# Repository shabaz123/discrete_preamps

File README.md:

# Discrete Amps

This repository contains  discrete audio amplifier designs intended primarily for HF receiver applications (speech bandwidth, not music).  

Each design includes:
- KiCad 10 Schematic and PCB files
- KiCad 10 SPICE Simulation Workbook
- Gerber files for fabrication  
- PDF schematic export and PCB screenshots for easy viewing without KiCad  

---

## Preamp K1

Designed by M. Kellett, this preamplifier is optimised for speech signals in HF receivers.

- **Gain:** ~28 dB  
- **Bandwidth (-3 dB):** ~150 Hz to 10 kHz (approximate)  
- **Use case:** Moderate gain front-end with relatively wide speech bandwidth  

### Schematic

### PCB Top

### PCB Underside

### PCB Render

---

## Preamp K2

Also designed by M. Kellett, this version provides higher gain and a slightly narrower bandwidth, making it suitable where additional amplification is required.

- **Gain:** ~45 dB  
- **Bandwidth (-3 dB):** ~100 Hz to 7 kHz (approximate)  
- **Use case:** Higher gain stage for weak signal amplification  

### Schematic

### PCB Top

### PCB Underside

### PCB Render

---

## Poweramp K1

Also designed by M. Kellett, this amplifier is a power stage, and it directly drives 8 ohm speakers, with low distortion (less than 0.5%) at 280 mW.

- **Gain:** ~27 dB  
- **Bandwidth (-3 dB):** ~50 Hz to 30 kHz (approximate)  
- **Use case:** Driving an 8-ohm speaker in a radio receiver  

### Schematic

### PCB Top

### PCB Underside

### PCB Render

---

## Notes

These designs are intended for experimentation and adaptation.

All components are easy to source. 

For the 9V power connection, the PCB will accomodate any 2-pin screw terminal block with 3.5 to 5.08 mm pin pitch. 

For the audio input and output, an AliExpress stereo audio jack socket can be used (only the tip and the screen is used, the ring is not connected). Alternatively, the audio connections can be made with 0.1" pin headers (they will fit in the same footprint, as there are extra holes for that). 

The potentiometer can be ALPS RK097 series (available from AliExpress), it has pins at 2.5 mm pitch, and a body width of 10 mm.

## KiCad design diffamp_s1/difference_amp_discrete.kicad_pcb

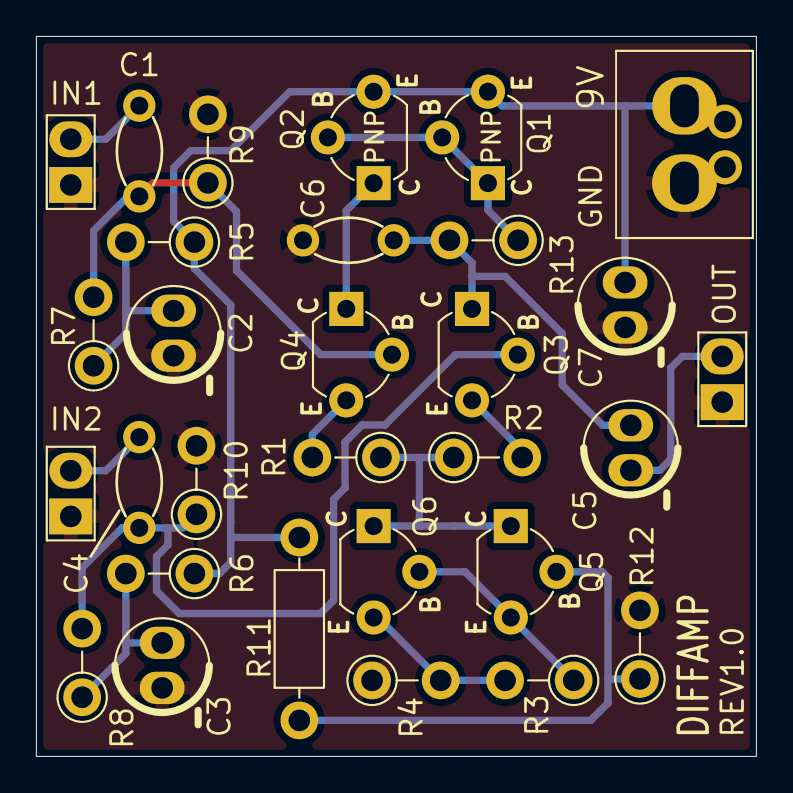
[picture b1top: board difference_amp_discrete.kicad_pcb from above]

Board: 2 copper layers, 40.0 x 40.0 mm, 30 parts (0 on the bottom side), 18 nets.

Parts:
C1, C4: 1u; C_Disc_T3.0mm_P5.0
C2, C3, C5, C7: 10u; CP_Radial_D5.0mm_P2.50mm
C6: 470p; C_Disc_T3.0mm_P5.0
J1: IN1; PinHeader_1x02_P2.54mm_Vertical
J2, J3: IN2; PinHeader_1x02_P2.54mm_Vertical
J4: 9VDC; TerminalBlock_2way-3.5-5.0mm
Q1, Q2: BC557; BJT_PNP_BC557
Q3, Q4, Q5, Q6: BC547; BJT_NPN_BC547
R1, R2, R3, R4: 470; R_Axial_L6.3mm_D2.5mm_P3.81mm_Vertical
R5, R6: 10k; R_Axial_L6.3mm_D2.5mm_P3.81mm_Vertical
R7, R8, R9, R10: 22k; R_Axial_L6.3mm_D2.5mm_P3.81mm_Vertical
R11: 2.7k; R_Axial_L6.3mm_D2.5mm_P10.16mm_Horiz
R12: 1k; R_Axial_L6.3mm_D2.5mm_P3.81mm_Vertical
R13: 3.3k; R_Axial_L6.3mm_D2.5mm_P3.81mm_Vertical

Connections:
0V: C2.2, C3.2, C6.1, C7.2, J1.1, J2.1, J3.1, J4.1, R4.1, R9.2, R10.2, R12.2
/IN1: C1.1, J1.2
/IN2: C4.2, J2.2
/OUT: C5.2, J3.2
unnamed: C2.1, R5.2, R7.1
unnamed: C3.1, R6.2, R8.1
unnamed: Q1.1 (C), Q1.2 (B), Q2.2 (B), R13.1
unnamed: Q2.1 (C), Q4.1 (C)
unnamed: C4.1, Q3.2 (B), R8.2, R10.1
unnamed: C5.1, C6.2, Q3.1 (C), R13.2
unnamed: Q3.3 (E), R2.2
unnamed: C1.2, Q4.2 (B), R7.2, R9.1
unnamed: Q4.3 (E), R1.2
unnamed: Q5.2 (B), R11.1, R12.1
unnamed: Q5.1 (C), Q6.1 (C), R1.1, R2.1
unnamed: Q5.3 (E), Q6.2 (B), R3.1
unnamed: Q6.3 (E), R3.2, R4.2
V+: C7.1, J4.2, Q1.3 (E), Q2.3 (E), R5.1, R6.1, R11.2

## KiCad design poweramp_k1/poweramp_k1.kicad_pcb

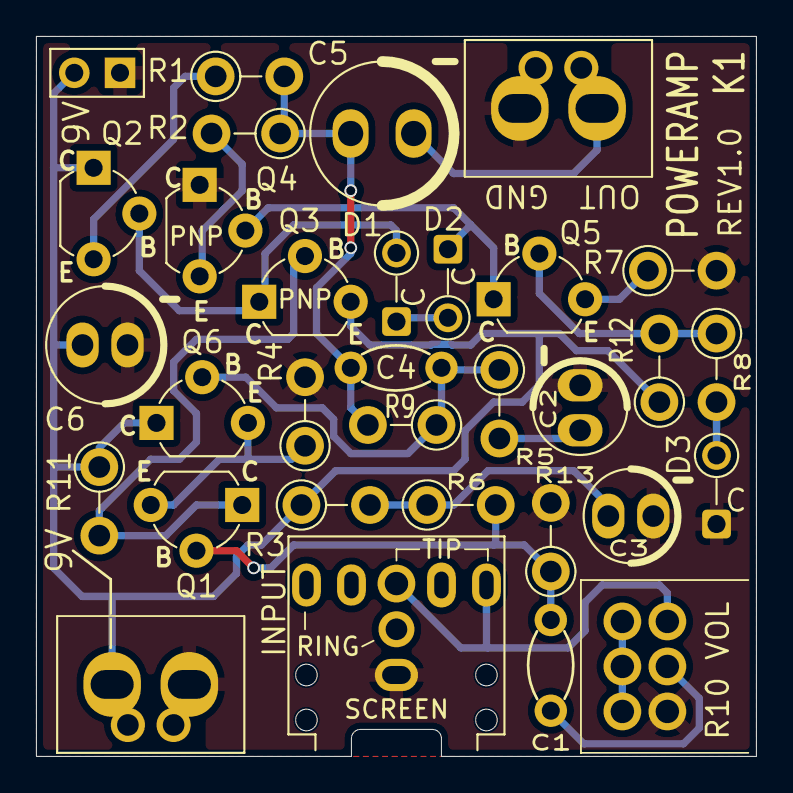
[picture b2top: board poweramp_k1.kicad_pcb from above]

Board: 2 copper layers, 40.0 x 40.0 mm, 32 parts (0 on the bottom side), 20 nets.

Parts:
C1: 220n; C_Disc_T3.0mm_P5.0
C2: 10u; CP_Radial_D5.0mm_P2.50mm
C3: 47u; CP_Radial_D5.0mm_P2.50mm
C4: 270p; C_Disc_T3.0mm_P5.0
C5: 470u; CP_Radial_D8mm_P3.5mm
C6: 100u; CP_Radial_D6.3mm_P2.50mm
D1, D2, D3: 1N4148; Diode-DO-35_1.75mmDia_P3.81mm_Vert_CathodeUp
J1: AudioJack_Stereo; Jack_3.5mm_CUI_SJ1-3525N_Horizontal
J3: 9VDC; TerminalBlock_2way-3.5-5.0mm
J4: PinHeader_1x02_P2.54mm_Vertical
J5: SPEAKER; TerminalBlock_2way-3.5-5.0mm
Q1, Q5, Q6: BC547; BJT_NPN_BC547
Q2: BC337-25; BJT_NPN_BC547
Q3: BC557; BJT_PNP_BC557
Q4: BC327-25; BJT_PNP_BC557
R1, R2: 2.2R; R_Axial_L6.3mm_D2.5mm_P3.81mm_Vertical
R3: 10k; R_Axial_L6.3mm_D2.5mm_P3.81mm_Vertical
R4: 1.5k; R_Axial_L6.3mm_D2.5mm_P3.81mm_Vertical
R5: 1k; R_Axial_L6.3mm_D2.5mm_P3.81mm_Vertical
R6: 33k; R_Axial_L6.3mm_D2.5mm_P3.81mm_Vertical
R7: 150R; R_Axial_L6.3mm_D2.5mm_P3.81mm_Vertical
R8: 2k; R_Axial_L6.3mm_D2.5mm_P3.81mm_Vertical
R9: 22k; R_Axial_L6.3mm_D2.5mm_P3.81mm_Vertical
R10: 22k; Potentiometer_RD701F
R11: 630R; R_Axial_L6.3mm_D2.5mm_P3.81mm_Vertical
R12: 27k; R_Axial_L6.3mm_D2.5mm_P3.81mm_Vertical
R13: 43k; R_Axial_L6.3mm_D2.5mm_P3.81mm_Vertical

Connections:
0V: C2.2, C3.2, C6.2, D3.1 (K), J1.S, J3.2, J4.1, J5.2, Q4.1 (C), R4.2, R7.2, R10.1, R13.2
/IN: J1.T, R10.3
/OUT: C5.2, J5.1
unnamed: C1.1, R10.2
unnamed: C2.1, R5.2
unnamed: C3.1, R3.2, R6.1
unnamed: C4.2, C5.1, R1.2, R2.1, R9.2
unnamed: D1.2 (A), Q2.2 (B), Q3.1 (C)
unnamed: D1.1 (K), D2.2 (A)
unnamed: D2.1 (K), Q4.2 (B), Q5.1 (C)
unnamed: D3.2 (A), R8.2
unnamed: C1.2, Q1.2 (B), R6.2, R13.1
unnamed: Q1.1 (C), Q3.2 (B), R11.2
unnamed: Q1.3 (E), Q6.3 (E), R4.1
unnamed: Q2.3 (E), R1.1
unnamed: Q4.3 (E), R2.2
unnamed: Q5.2 (B), R8.1, R12.2
unnamed: Q5.3 (E), R7.1
unnamed: C4.1, Q6.2 (B), R5.1, R9.1
V+: C6.1, J3.1, J4.2, Q2.1 (C), Q3.3 (E), Q6.1 (C), R3.1, R11.1, R12.1

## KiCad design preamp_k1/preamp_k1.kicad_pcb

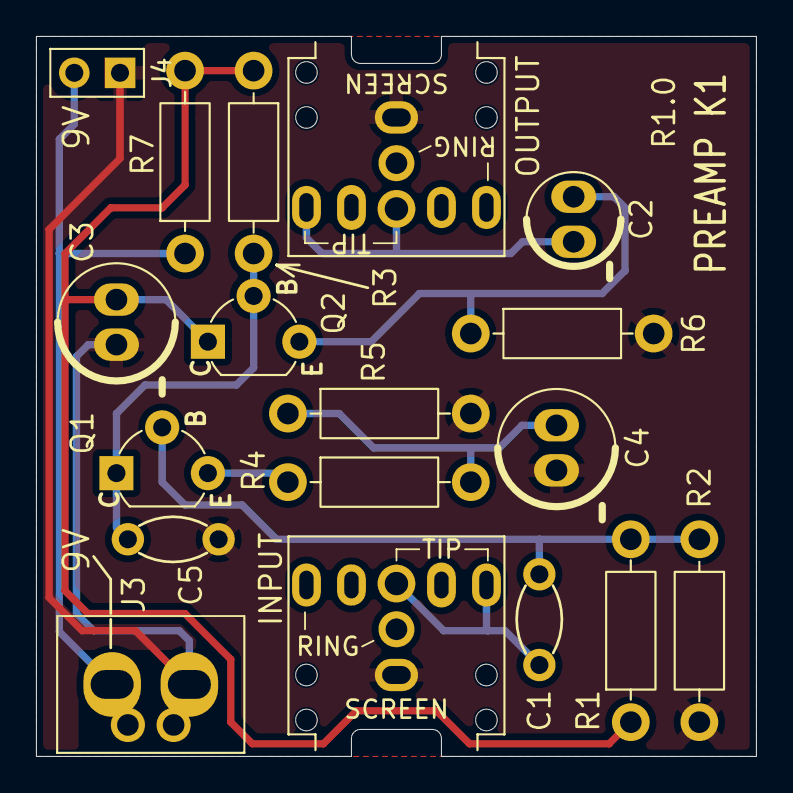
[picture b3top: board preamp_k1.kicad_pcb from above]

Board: 2 copper layers, 40.0 x 40.0 mm, 18 parts (0 on the bottom side), 10 nets.

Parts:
C1: 100n; C_Disc_T3.0mm_P5.0
C2: 4.7u; CP_Radial_D5.0mm_P2.50mm
C3: 47u; CP_Radial_D6.3mm_P2.50mm
C4: 4.7u; CP_Radial_D6.3mm_P2.50mm
C5: 10n; C_Disc_T3.0mm_P5.0
J1, J2: AudioJack_Stereo; Jack_3.5mm_CUI_SJ1-3525N_Horizontal
J3: 9VDC; TerminalBlock_2way-3.5-5.0mm
J4: PinHeader_1x02_P2.54mm_Vertical
Q1, Q2: BC549; BJT_NPN_BC547
R1: 100k; R_Axial_L6.3mm_D2.5mm_P10.16mm_Horiz
R2: 33k; R_Axial_L6.3mm_D2.5mm_P10.16mm_Horiz
R3: 2.2k; R_Axial_L6.3mm_D2.5mm_P10.16mm_Horiz
R4: 47R; R_Axial_L6.3mm_D2.5mm_P10.16mm_Horiz
R5: 910R; R_Axial_L6.3mm_D2.5mm_P10.16mm_Horiz
R6: 4.7k; R_Axial_L6.3mm_D2.5mm_P10.16mm_Horiz
R7: 1.2k; R_Axial_L6.3mm_D2.5mm_P10.16mm_Horiz

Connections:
0V: C3.2, C4.2, C5.1, J1.S, J2.S, J3.2, J4.1, R2.2, R5.2, R6.2
/IN: C1.1, J1.T
/OUT: C2.2, J2.T
unnamed: C4.1, R4.2, R5.1
unnamed: C1.2, Q1.2 (B), R1.2, R2.1
unnamed: C5.2, Q1.1 (C), Q2.2 (B), R3.2
unnamed: Q1.3 (E), R4.1
unnamed: C3.1, Q2.1 (C), R1.1, R3.1, R7.2
unnamed: C2.1, Q2.3 (E), R6.1
V+: J3.1, J4.2, R7.1

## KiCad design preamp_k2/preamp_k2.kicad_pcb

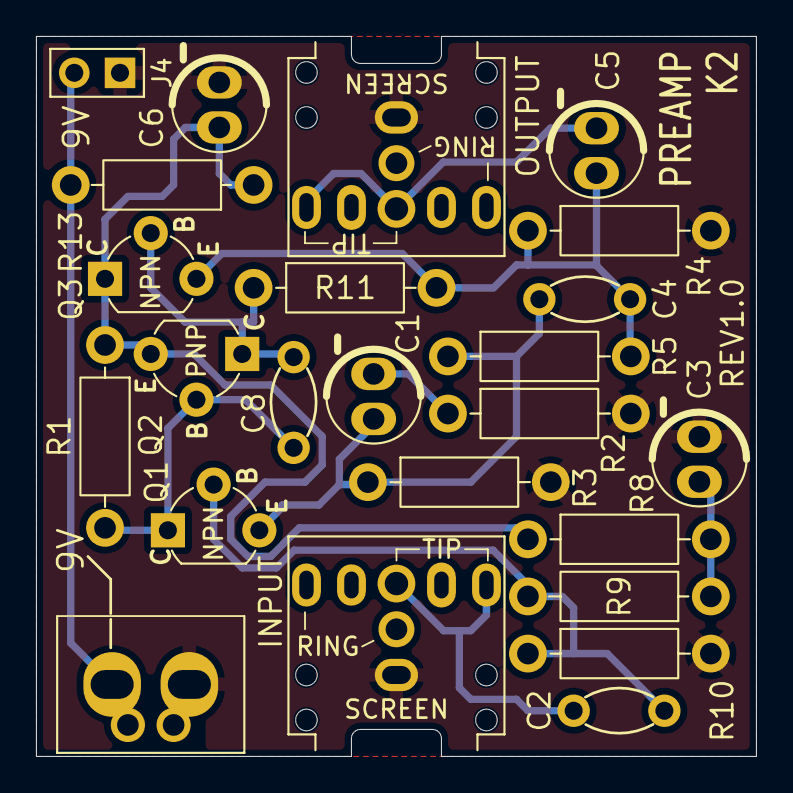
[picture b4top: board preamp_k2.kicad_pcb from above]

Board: 2 copper layers, 40.0 x 40.0 mm, 24 parts (0 on the bottom side), 12 nets.

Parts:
C1, C3, C6: 22u; CP_Radial_D5.0mm_P2.50mm
C2: 100n; C_Disc_T3.0mm_P5.0
C4: 2.2n; C_Disc_T3.0mm_P5.0
C5: 4.7u; CP_Radial_D5.0mm_P2.50mm
C8: 220p; C_Disc_T3.0mm_P5.0
J1, J2: AudioJack_Stereo; Jack_3.5mm_CUI_SJ1-3525N_Horizontal
J3: 9VDC; TerminalBlock_2way-3.5-5.0mm
J4: PinHeader_1x02_P2.54mm_Vertical
Q1, Q3: BC549; BJT_NPN_BC547
Q2: BC559; BJT_PNP_BC557
R1: 5.6k; R_Axial_L6.3mm_D2.5mm_P10.16mm_Horiz
R2: 82R; R_Axial_L6.3mm_D2.5mm_P10.16mm_Horiz
R3: 2.7k; R_Axial_L6.3mm_D2.5mm_P10.16mm_Horiz
R4, R11: 3.9k; R_Axial_L6.3mm_D2.5mm_P10.16mm_Horiz
R5: 16k; R_Axial_L6.3mm_D2.5mm_P10.16mm_Horiz
R8: 91k; R_Axial_L6.3mm_D2.5mm_P10.16mm_Horiz
R9: 180k; R_Axial_L6.3mm_D2.5mm_P10.16mm_Horiz
R10: 56k; R_Axial_L6.3mm_D2.5mm_P10.16mm_Horiz
R13: 560R; R_Axial_L6.3mm_D2.5mm_P10.16mm_Horiz

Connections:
0V: C3.2, C6.2, J1.S, J2.S, J3.2, J4.1, R2.2, R3.2, R4.2, R10.2
/IN: C2.1, J1.T
/OUT: C5.2, J2.T
unnamed: C1.2, R2.1
unnamed: C3.1, R8.2, R9.1
unnamed: C2.2, Q1.2 (B), R9.2, R10.1
unnamed: C8.1, Q1.1 (C), Q2.2 (B), R1.2
unnamed: C1.1, C4.1, Q1.3 (E), R3.1, R5.1
unnamed: C8.2, Q2.1 (C), Q3.2 (B), R11.1
unnamed: C6.1, Q2.3 (E), Q3.1 (C), R1.1, R8.1, R13.1
unnamed: C4.2, C5.1, Q3.3 (E), R4.1, R5.2, R11.2
V+: J3.1, J4.2, R13.2

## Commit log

2026-04-15 Rename project from 'Discrete Preamps' to 'Discrete Amps'
2026-04-15 Correct capitalization in README.md
2026-04-15 Add Poweramp K1 section to README
